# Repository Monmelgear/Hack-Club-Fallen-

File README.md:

# Hack-Club-Fallen-

Our project is a delivery drone that can be used to transfer medical items or other items from one location to another. To use it you must control it via the controlled which uses joysticks to control its movements on all 3 axises and there is a button on the controller to open and close the drones claw to grab items. You will be able to see through the drones pov via the fpv camera installed in it. We made this because we wanted to build something cool, we have little to no prior knowledge of hardware and wanted to start with a challenge so we can attend hackathons in the future. This project serves as a way to learn as much as we can about hardware and build something we always wanted to, a drone.

## Drone assembly

Open the [editable FreeCAD project](Design%20Review/Drone%20assembly.FCStd) to inspect individual components and edit the camera shoe and PCB rails. The original camera head uses the strap adapter. The electronics and propeller blades are clearance models.

[Blender source](Design%20Review/Drone%20assembly.blend) · [Assembly STEP archive](Design%20Review/Drone%20assembly.step.zip) · [Electronics view](Design%20Review/Electronics%20placement.png) · [Mounts and fit notes](Design%20Review/Design%20review.md) · [Bill of materials](Design%20Review/Project%20BOM.csv)

Here is our PCB

[Editable KiCad project](PCB/Claw%20Board.kicad_pro) 

This is the Schematic or as some calls it the wiring diagram

[Circuit schematic PDF](PCB/Schematic.pdf)

For a build submission, also:

Link your demo video
Add images of the final product

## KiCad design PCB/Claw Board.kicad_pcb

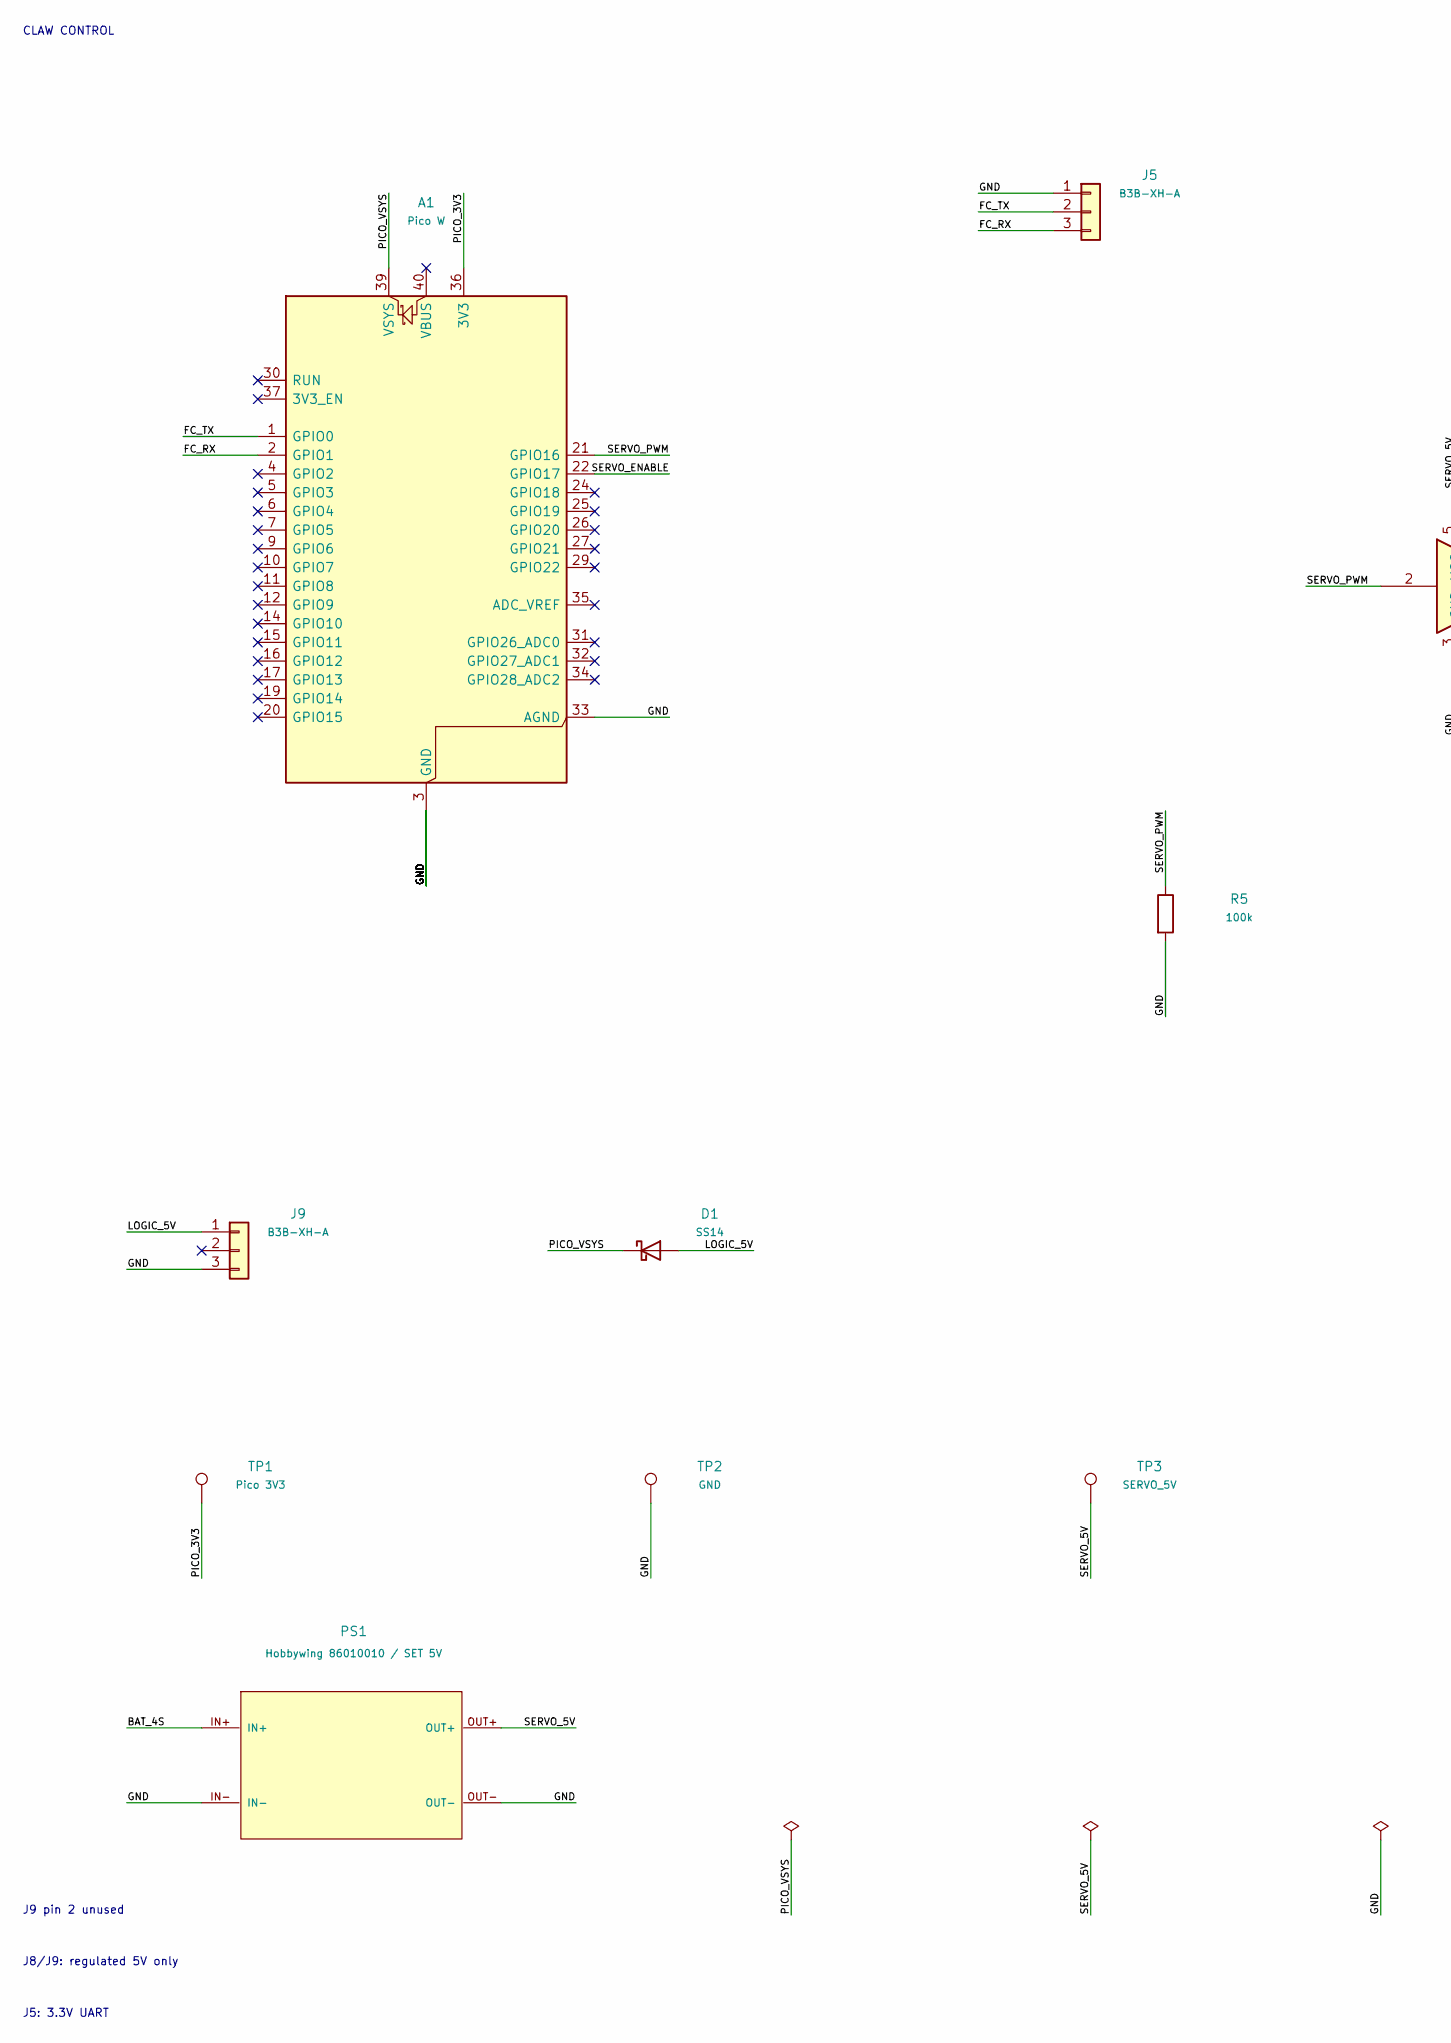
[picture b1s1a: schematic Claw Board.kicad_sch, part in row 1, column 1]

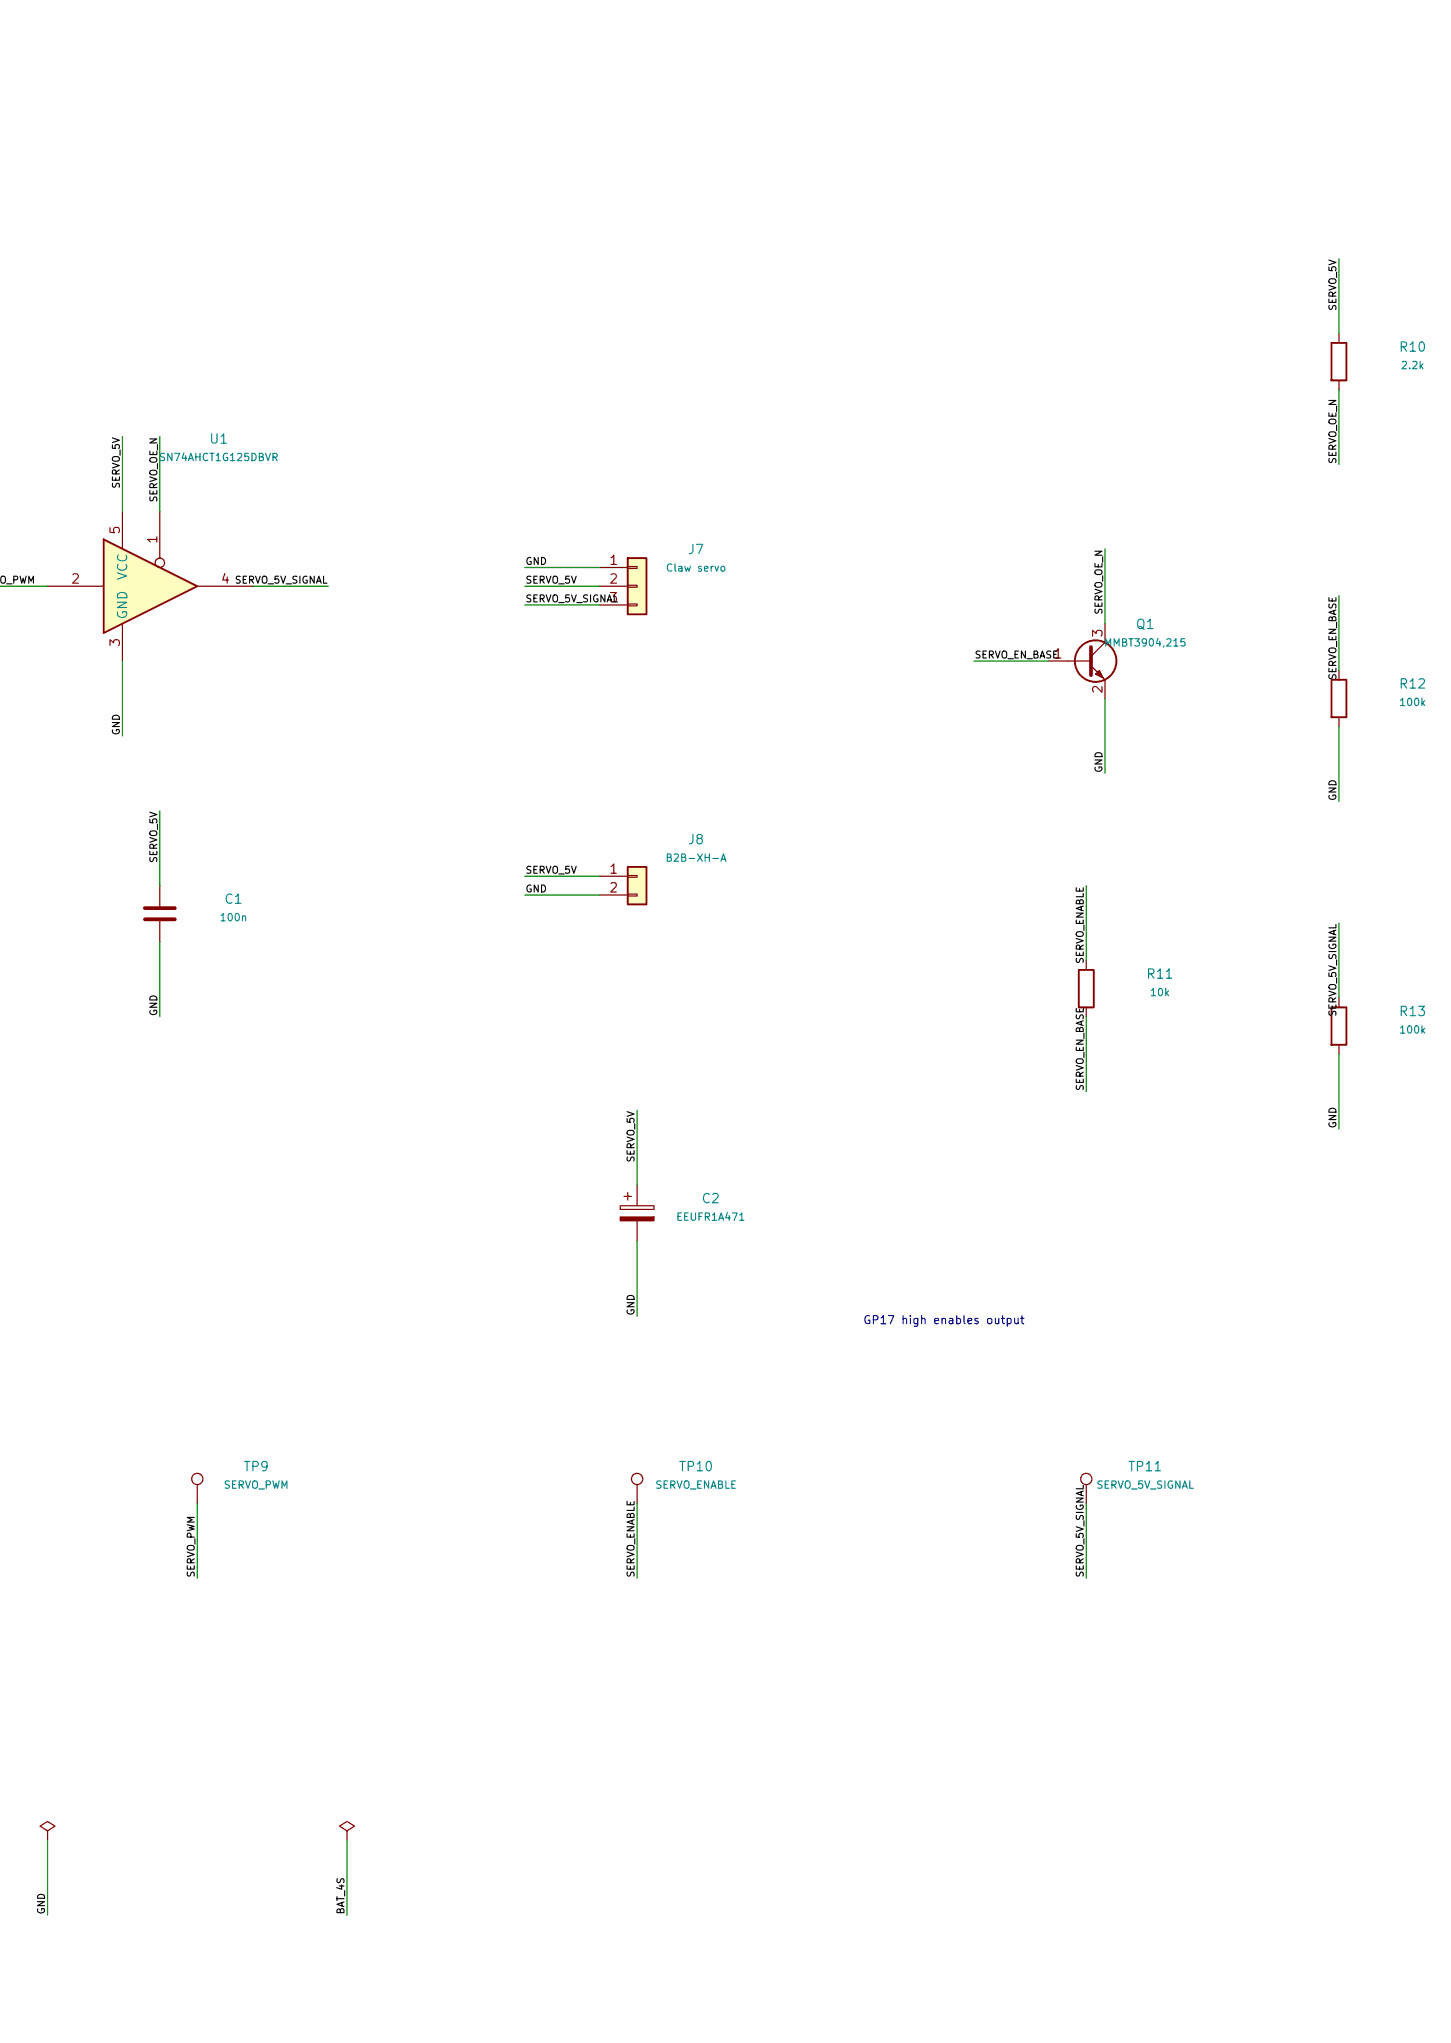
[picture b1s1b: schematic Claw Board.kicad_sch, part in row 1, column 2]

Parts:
A1: Pico W; Pico_W_Notch_THT
C1: 100n; C_0805_2012Metric
C2: EEUFR1A471; CP_Radial_D8.0mm_P3.50mm
D1: SS14; D_SMA
J5, J9: B3B-XH-A; JST_XH_B3B-XH-A_1x03_P2.50mm_Vertical
J7: Claw servo; PinHeader_1x03_P2.54mm_Vertical
J8: B2B-XH-A; JST_XH_B2B-XH-A_1x02_P2.50mm_Vertical
PS1: Hobbywing 86010010 / SET 5V
Q1: MMBT3904,215; SOT-23
R5, R12, R13: 100k; R_0805_2012Metric
R10: 2.2k; R_0805_2012Metric
R11: 10k; R_0805_2012Metric
TP1: Pico 3V3; TestPoint_Pad_D1.0mm
TP2: GND; TestPoint_Pad_D1.0mm
TP3: SERVO_5V; TestPoint_Pad_D1.0mm
TP9: SERVO_PWM; TestPoint_Pad_D1.0mm
TP10: SERVO_ENABLE; TestPoint_Pad_D1.0mm
TP11: SERVO_5V_SIGNAL; TestPoint_Pad_D1.0mm
U1: SN74AHCT1G125DBVR; SOT-23-5

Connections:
/FC_RX: A1.2 (GPIO1), J5.3
/FC_TX: A1.1 (GPIO0), J5.2
/GND: A1.3 (GND), A1.8 (GND), A1.13 (GND), A1.18 (GND), A1.23 (GND), A1.28 (GND), A1.33 (AGND), A1.38 (GND), C1.2, C2.2, J5.1, J7.1, J8.2, J9.3, PS1.IN-, PS1.OUT-, Q1.2 (E), R5.2, R12.2, R13.2, TP2.1, U1.3 (GND)
/LOGIC_5V: D1.2 (A), J9.1
/PICO_3V3: A1.36 (3V3), TP1.1
/PICO_VSYS: A1.39 (VSYS), D1.1 (K)
/SERVO_5V: C1.1, C2.1, J7.2, J8.1, PS1.OUT+, R10.1, TP3.1, U1.5 (VCC)
/SERVO_5V_SIGNAL: J7.3, R13.1, TP11.1, U1.4
/SERVO_ENABLE: A1.22 (GPIO17), R11.1, TP10.1
/SERVO_EN_BASE: Q1.1 (B), R11.2, R12.1
/SERVO_OE_N: Q1.3 (C), R10.2, U1.1
/SERVO_PWM: A1.21 (GPIO16), R5.1, TP9.1, U1.2

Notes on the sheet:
CLAW CONTROL
GP17 high enables output
J9 pin 2 unused
J8/J9: regulated 5V only
J5: 3.3V UART

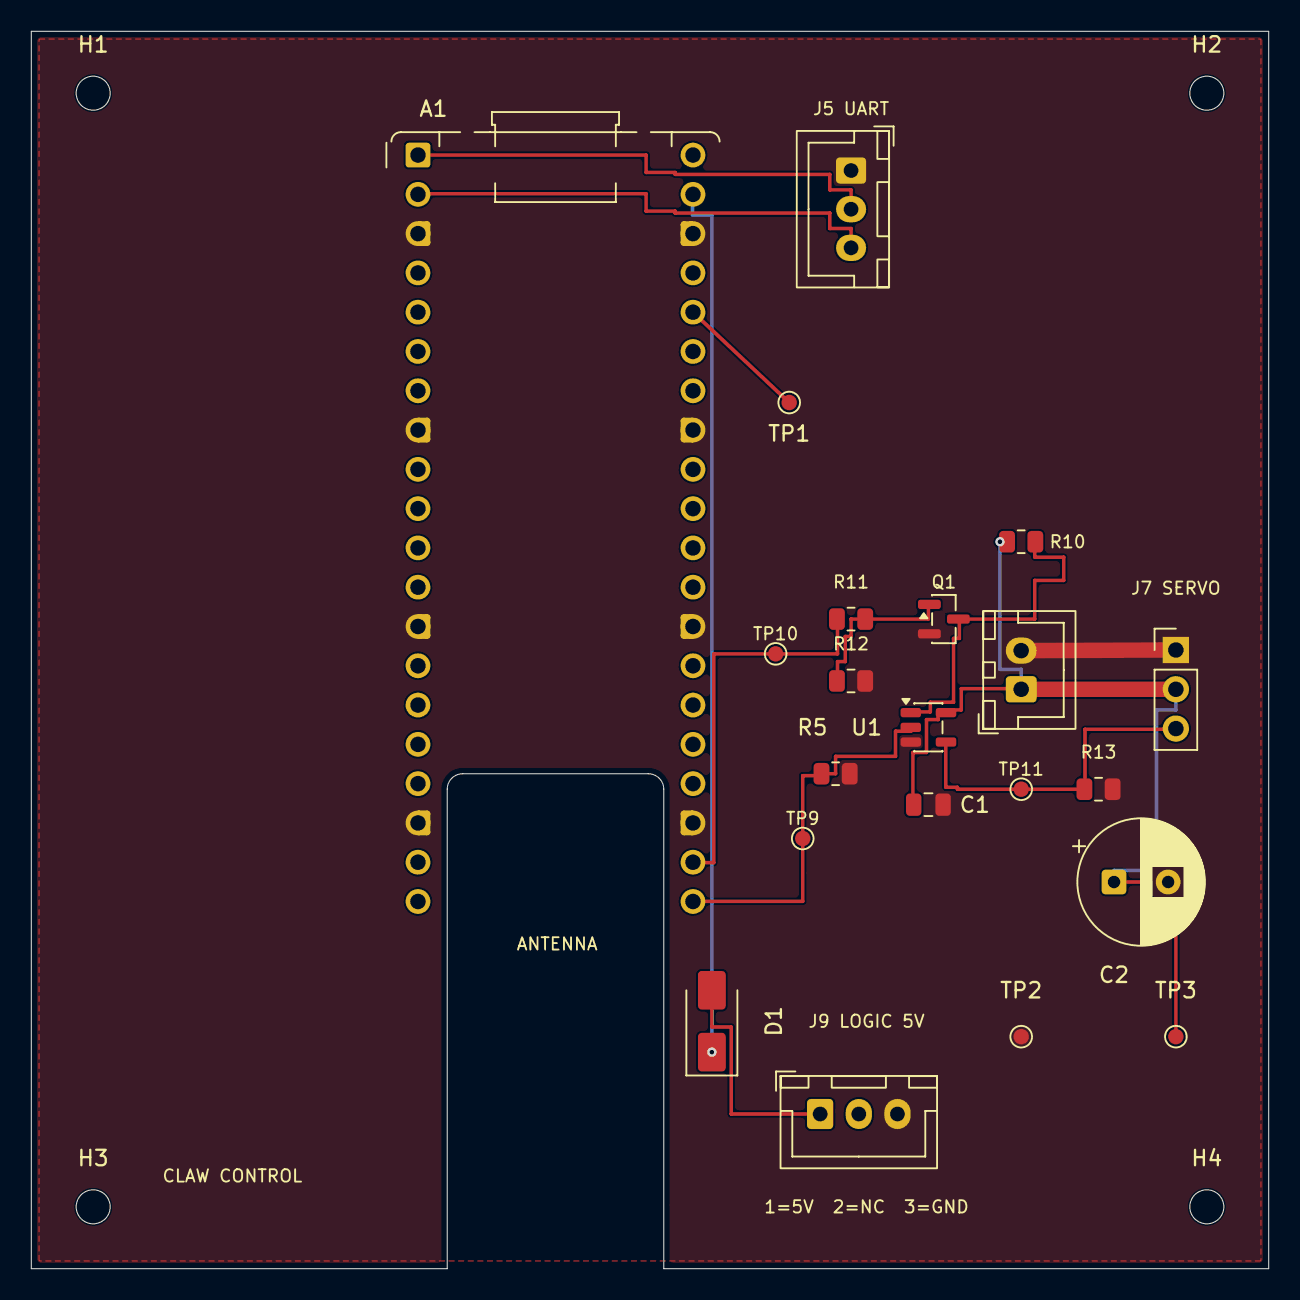
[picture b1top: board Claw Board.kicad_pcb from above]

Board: 2 copper layers, 80.0 x 80.0 mm, 25 parts (0 on the bottom side), 12 nets.

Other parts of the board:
H1, H2, H3, H4: MountingHole_2.2mm_M2

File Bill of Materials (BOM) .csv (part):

"Section","Item","Quantity","Estimated line cost USD","Source or distributor search","Fit or purchasing check","Availability evidence","Delivery status"
"Electronics","iFlight XING 2005 2550KV","4","$103.96","https://pyrodrone.com/products/iflight-xing-2005-4-6s-fpv-un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","12 mm M2 mount; verify shaft retaining clip and screw engagement. Four exact variants needed.","US listing; exact stock of four and checkout ETA unconfirmed","No dated delivery to destination"
"Electronics","Airbot Fenix G4 4-in-1 35A","1","$89.99","https://www.racedayquads.com/products/airbot-fenix-g4-4-6s-a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","4S acceptable; bench-confirm free UART, mounting/grommets and 5V current budget.","Seller listing showed stock","No dated delivery to destination"
"Electronics","iFlight Nazgul 5030 tri-blade","1 pack; install 2 CW and 2 CCW","$8.99 estimate","https://shop.iflight.com/nazgul-5030-tri-blade-prop-cw-ccw-3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","Manufacturer specifies this T-mount for XING 2005. Retain this exact prop.","Variant / quantity unconfirmed","No dated delivery to destination"
"Electronics","Tattu FunFly 4S 1300mAh 100C XT60","1","$19.59","https://genstattu.com/ta-ff-100c-1300-4s1p.html","130 A nameplate. Ground shipping. Pack envelope 78 x 37 x 30.5 mm maximum published. Check actual weight, sag, wiring temperatures and balance.","Supplier listed stock; dated ETA unconfirmed","No dated delivery to destination"
"Electronics","RadioMaster T8L ELRS FCC","1","$45.99","https://pyrodrone.com/products/radiomaster-t8l-rc-transmitte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","FCC ELRS variant; bind and verify failsafe.","Variant / quantity unconfirmed","No dated delivery to destination"
"Electronics","Molicel P30B 18650","1 pair","$22.99","https://www.racedayquads.com/products/molicel-p30b-18650-300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","Two cells for radio; ground delivery.","Seller listing showed stock","No dated delivery to destination"
"Electronics","RadioMaster RP1 V2 2.4GHz ELRS","1","$24.99","https://www.racedayquads.com/products/radiomaster-rp1-v2-2-4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","Match ELRS major version; verify receiver UART.","Seller listing showed stock","No dated delivery to destination"
"Electronics","ToolkitRC M6AC","1","$71.99","https://www.racedayquads.com/products/toolkitrc-m6ac-300w-15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","1-6S charger; check balance plug and AC cord.","Seller listing showed stock","No dated delivery to destination"
"Electronics","TowerPro MG92B","1","$11.95","https://www.adafruit.com/product/2307","5V supply and 5V signal; torque under actual load unverified.","Seller listing showed stock","No dated delivery to destination"
"Electronics","Hobbywing 86010010 UBEC 3A","1","$8.99","https://www.hobbywingdirect.com/collections/accessories/prod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","Set to 5V. Verify stall current and common ground.","Variant / quantity unconfirmed","No dated delivery to destination"
"Electronics","FYS 4.3 inch analog monitor","1","$92.99","https://www.racedayquads.com/products/fys-40ch-5-8ghz-divers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","Match analog channel; mounting bracket for handheld still needed.","Seller listing showed stock","No dated delivery to destination"
"Electronics","RunCam Nano 4 NTSC","1","$25.99","https://pyrodrone.com/products/runcam-nano-4-1-3-800tvl-155-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","14mm camera fit, cable, lens opening and field of view unverified.","Seller listing showed stock","No dated delivery to destination"
"Electronics","GEPRC RAD Whoop 5.8GHz VTX","1","$36.99","https://pyrodrone.com/collections/analog-vtx/products/geprc-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","Verify supply, antenna, connector and common channel.","Seller listing showed stock","No dated delivery to destination"
"Electronics","MaxAmps XT60 male 12 AWG power lead","1","$15.00","https://maxamps.com/products/maxamps-xt60-male-connector-wit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","Check FC pad size, polarity, strain relief and lead current under load.","Unconfirmed","No dated delivery to destination"
"Electronics","Raspberry Pi Pico W SC0918","1","~$7.65","https://www.digikey.com/en/products/detail/raspberry-pi/SC09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","Two 1x20 headers if unpinned. GP16 signal, GP17 enable, GP0/1 UART.","Seller listing showed stock","No dated delivery to destination"
"PCB","C1 100n","1","","https://www.digikey.com/en/products/detail/murata-electronic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","Capacitor_SMD:C_0805_2012Metric; verify orderable package","Unverified","No dated delivery to destination"
"PCB","C2 EEUFR1A471","1","","https://industrial.panasonic.com/ww/products/pt/aluminum-cap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","Capacitor_THT:CP_Radial_D8.0mm_P3.50mm; verify orderable package","Unverified","No dated delivery to destination"
"PCB","D1 SS14","1","","https://www.digikey.com/en/products/detail/vishay-general-se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","Diode_SMD:D_SMA; verify orderable package","Unverified","No dated delivery to destination"
"PCB","J5 B3B-XH-A","1","","https://www.digikey.com/en/products/detail/jst-sales-america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","Connector_JST:JST_XH_B3B-XH-A_1x03_P2.50mm_Vertical; verify orderable package","Unverified","No dated delivery to destination"
"PCB","J7 Samtec TSW-103-07-G-S","1","","https://www.digikey.com/en/products/detail/samtec-inc/TSW-10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","Connector_PinHeader_2.54mm:PinHeader_1x03_P2.54mm_Vertical; verify orderable package","Unverified","No dated delivery to destination"
"PCB","J8 B2B-XH-A","1","","https://www.digikey.com/en/products/detail/jst-sales-america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","Connector_JST:JST_XH_B2B-XH-A_1x02_P2.50mm_Vertical; verify orderable package","Unverified","No dated delivery to destination"
"PCB","J9 B3B-XH-A","1","","https://www.digikey.com/en/products/detail/jst-sales-america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","Connector_JST:JST_XH_B3B-XH-A_1x03_P2.50mm_Vertical; verify orderable package","Unverified","No dated delivery to destination"
"PCB","Q1 MMBT3904,215","1","","https://www.digikey.com/en/products/detail/nexperia-usa-inc/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","Package_TO_SOT_SMD:SOT-23; verify orderable package","Unverified","No dated delivery to destination"
"PCB","R5 100k","1","","https://www.digikey.com/en/products/detail/yageo/RC0805FR-07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","Resistor_SMD:R_0805_2012Metric; verify orderable package","Unverified","No dated delivery to destination"
"PCB","R10 2.2k","1","","https://www.digikey.com/en/products/detail/yageo/RC0805FR-07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","Resistor_SMD:R_0805_2012Metric; verify orderable package","Unverified","No dated delivery to destination"
"PCB","R11 10k","1","","https://www.digikey.com/en/products/detail/yageo/RC0805FR-07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","Resistor_SMD:R_0805_2012Metric; verify orderable package","Unverified","No dated delivery to destination"
"PCB","R12 100k","1","","https://www.digikey.com/en/products/detail/yageo/RC0805FR-07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","Resistor_SMD:R_0805_2012Metric; verify orderable package","Unverified","No dated delivery to destination"
"PCB","R13 100k","1","","https://www.digikey.com/en/products/detail/yageo/RC0805FR-07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","Resistor_SMD:R_0805_2012Metric; verify orderable package","Unverified","No dated delivery to destination"
"PCB","U1 SN74AHCT1G125DBVR","1","","https://www.ti.com/product/SN74AHCT1G125/part-details/SN74AH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","Package_TO_SOT_SMD:SOT-23-5; verify orderable package","Unverified","No dated delivery to destination"
"Assembly supplies","Bare custom PCB","1 populated board; quote minimum lot","","https://github.com/Monmelgear/Hack-Club-Fallen-/blob/main/PC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","Verify dimensions, ownership and sourcing","Unverified","No dated delivery to destination"
"Assembly supplies","1x20 2.54mm Pico headers","2","","https://www.adafruit.com/product/392","Cut two 20-pin sections from separate strips if using the through-hole mount.","Unverified","No dated delivery to destination"
"Assembly supplies","XHP-3 mating housing","2","","https://www.digikey.com/en/products/detail/jst-sales-america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","Verify dimensions, ownership and sourcing","Unverified","No dated delivery to destination"
"Assembly supplies","XHP-2 mating housing","1","","https://www.digikey.com/en/products/detail/jst-sales-america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","Verify dimensions, ownership and sourcing","Unverified","No dated delivery to destination"
"Assembly supplies","XH crimp contacts for selected wire gauge","7 installed","","https://www.digikey.com/en/products/detail/jst-sales-america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","SXH-001T-P0.6 accepts 22–28 AWG. J9 pin 2 is unused.","Unverified","No dated delivery to destination"
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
